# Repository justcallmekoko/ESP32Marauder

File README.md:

<!------>
<!------>
<!------>
<!---Shields/Badges https://shields.io/--->

# ESP32 Marauder

<p align="center">
  <b>A suite of WiFi/Bluetooth offensive and defensive tools for the ESP32</b>
  <br><br>

  <br>

  <br><br>
</p>

## Getting Started
Download the [latest release](https://github.com/justcallmekoko/ESP32Marauder/releases/latest) of the firmware.  

Check out the project [wiki](https://github.com/justcallmekoko/ESP32Marauder/wiki) for a full overview of the ESP32 Marauder

## FCC module identifiers

The Device Info screen reports the FCC ID of the radio module fitted to supported JustCallMeKoko hardware. This is the module identifier, not a claim that every carrier-board or enclosure configuration has a separate end-product grant.

| Hardware | Radio module | FCC ID |
| --- | --- | --- |
| Marauder v8, Marauder Mini v3, C5 Wardriver, C5 LowKey, BFFB v2 | ESP32-C5-WROOM-U | `2AC7Z-ESPC5WROOMU` |
| Marauder v4, v6, v6.1, v7, original Mini, Marauder Kit | ESP32-WROOM-32U | `2AC7Z-ESP32WROOM32U` |
| BFFB / Marauder Dev Board Pro | ESP32-WROOM-32E | `2AC7Z-ESP32WROOM32E` |

The legacy mappings are the closest modular approvals for the modules specified by the repository hardware designs. Confirm the module marking on a physical unit before using an FCC ID for labeling or compliance documentation. Third-party targets display `See hardware label` because their module or complete-device certification can vary by production revision.

# For Sale Now
You can buy the ESP32 Marauder using [this link](https://www.justcallmekokollc.com)

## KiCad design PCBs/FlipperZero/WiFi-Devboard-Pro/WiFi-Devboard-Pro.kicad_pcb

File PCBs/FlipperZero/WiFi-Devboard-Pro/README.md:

# Parts

- Header Pin x8: [C2883805](https://www.lcsc.com/product-detail/Pin-Headers_XKB-Connectivity-X6511WVS-08H-C60D48R1_C2883805.html)
- Header Pin x10: [C2883807](https://www.lcsc.com/product-detail/Pin-Headers_XKB-Connectivity-X6511WVS-10H-C60D48R1_C2883807.html)
- Alternative Header: [M20-8771246](https://www.mouser.com/ProductDetail/Harwin/M20-8771246?qs=WS5Jv%252B%252Bx1qWzrNY%252Bb2U9JQ%3D%3D&countryCode=US&currencyCode=USD)
  - or [M20-8771042](https://www.mouser.com/ProductDetail/Harwin/M20-8771042?qs=%252Bk6%2F5FB6qrlBSpg9%252Bi11Bg%3D%3D)
- Light Pipe: [PLP2-188](https://www.digikey.com/en/products/detail/bivar-inc/PLP2-188/5721973?utm_medium=email&utm_source=oce&utm_campaign=4251_OCE23RT&utm_content=productdetail_US&utm_cid=2955578&so=79456987&mkt_tok=MDI4LVNYSy01MDcAAAGJOBaFWa7m6RHsJZT6mWcYRd9LRyXmqis92EV7j5ftyM5NuNOSOPqUp292m0P5E3FKrEWCFuvb9fObSzuSvVMsopuOMPjO46ylCAR1IzCL)
- M2x6mm Round Top Screw: [97763A407](https://www.mcmaster.com/97763A407/)
- M2x8mm Countersunk Screw: [91294A005](https://www.mcmaster.com/91294A005/)
- M2 Threaded Insert: [94180A307](https://www.mcmaster.com/94180A307/)

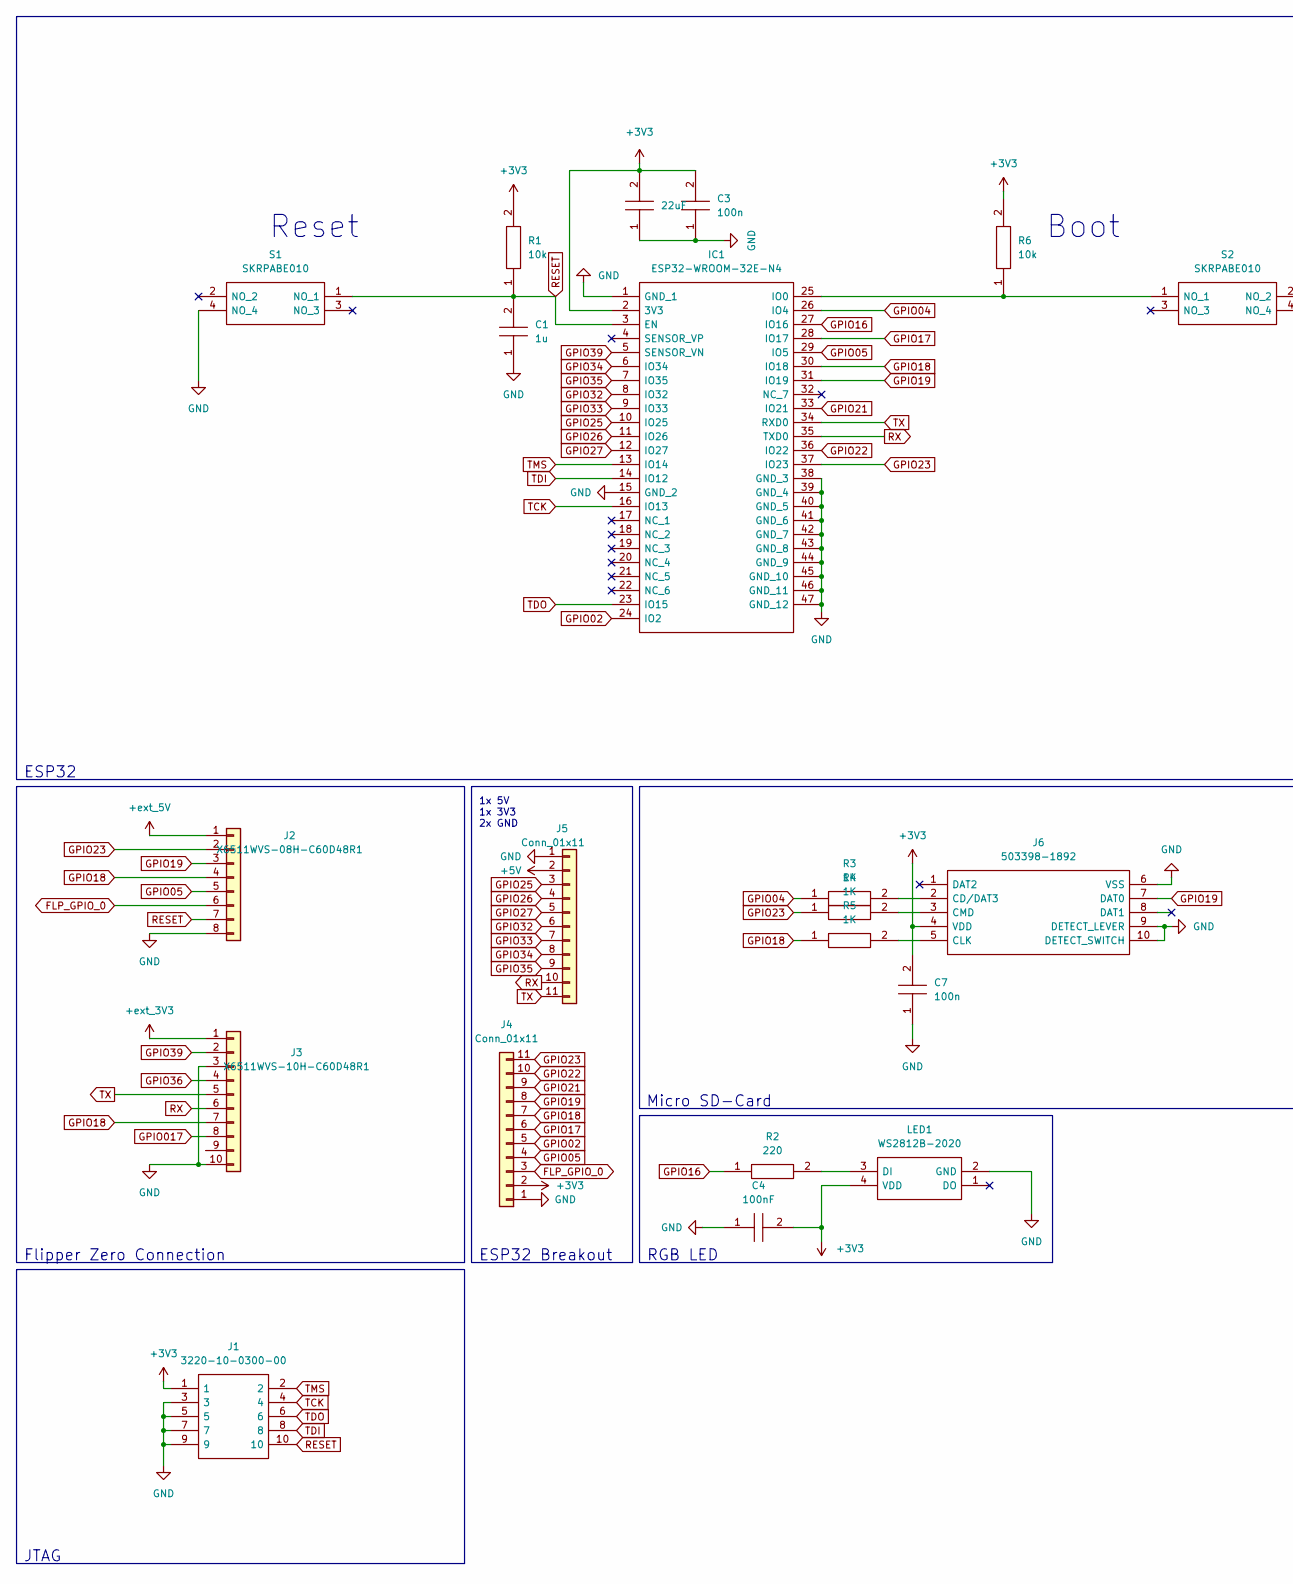
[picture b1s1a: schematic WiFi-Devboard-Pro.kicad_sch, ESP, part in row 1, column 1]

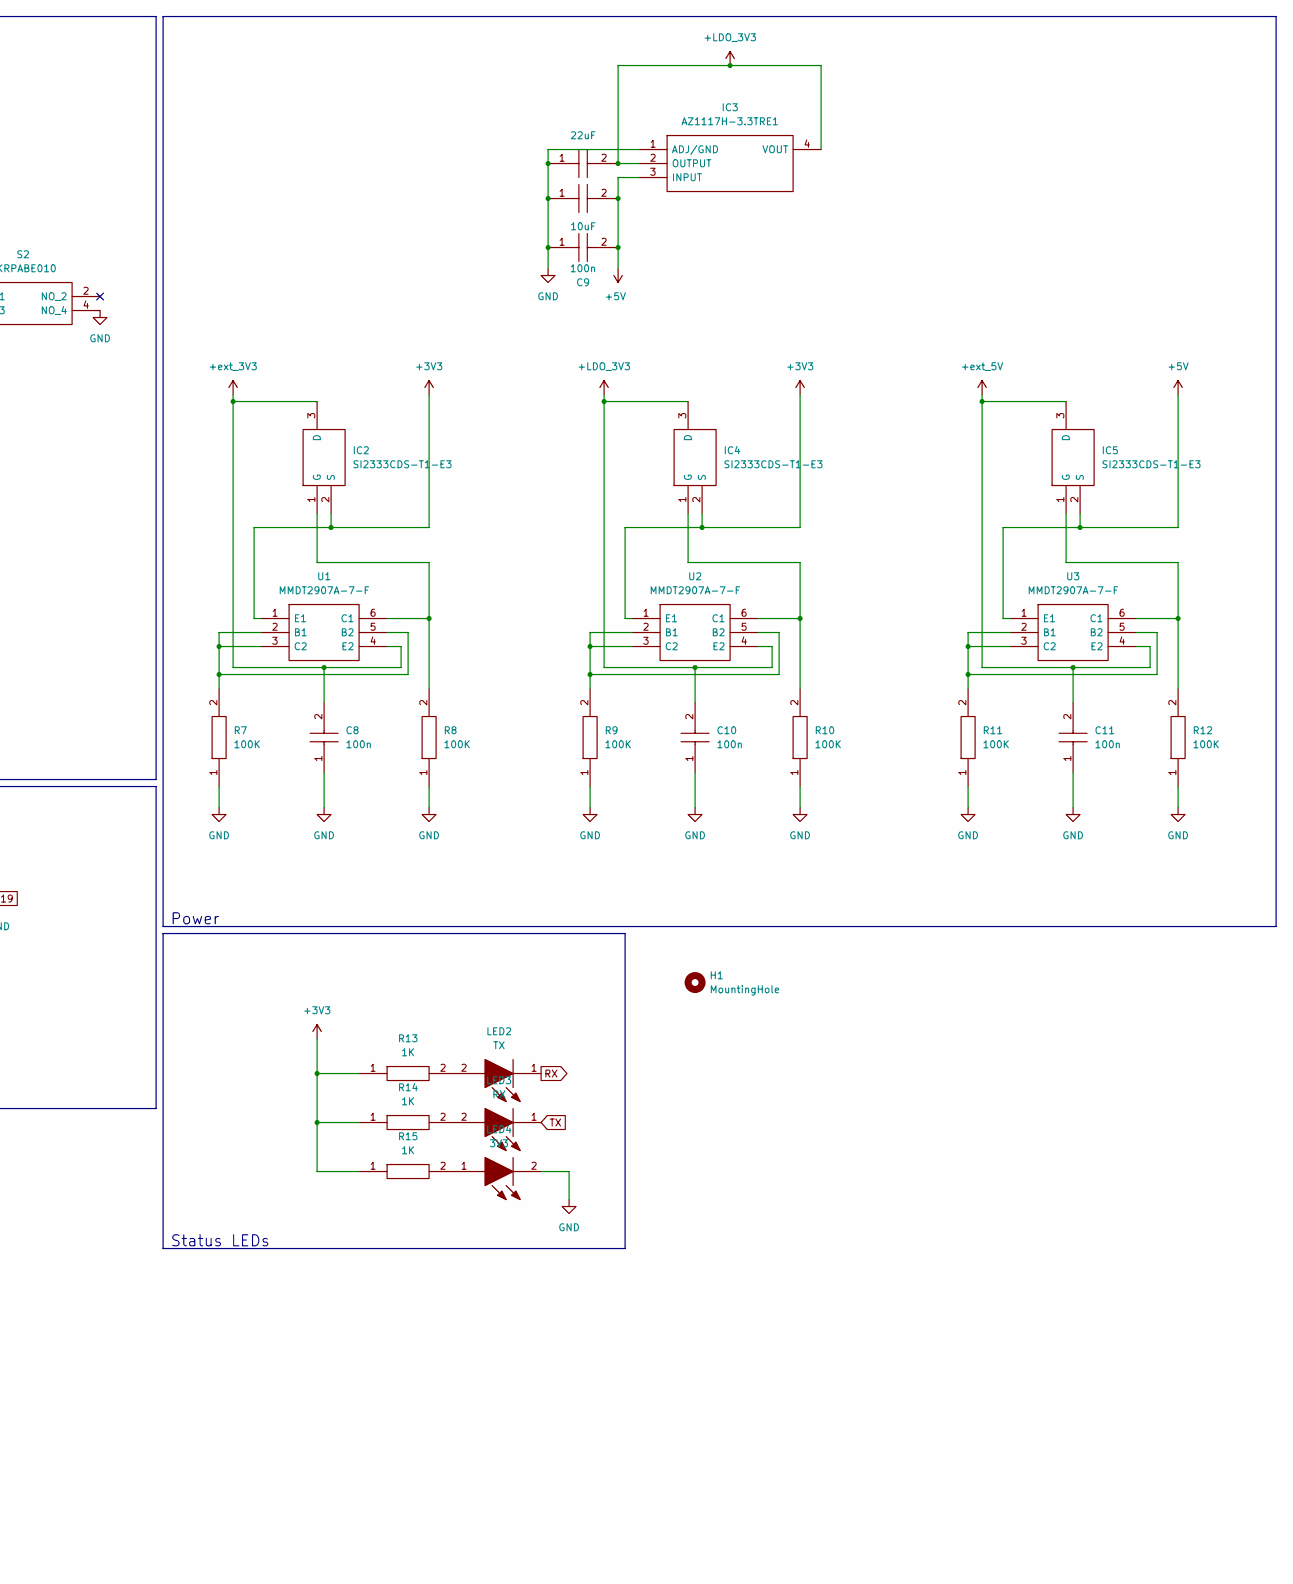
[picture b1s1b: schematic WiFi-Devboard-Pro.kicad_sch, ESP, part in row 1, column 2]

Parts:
C1: 1u; 0402; Manufacturer_Part_Number CL05A105KA5NQNC; Mouser Part Number 187-CL05A105KA5NQNC
C2, C5: 22uF; 0402; Manufacturer_Part_Number CM05X5R226M06AH080; Mouser Part Number 346-CM05X5R226M6AH80
C3, C7, C8, C9, C10, C11: 100n; 0402; Manufacturer_Part_Number CL05B104KO5NNNC; Mouser Part Number 187-CL05B104KO5NNNC
C4: 100nF; 0402; Manufacturer_Part_Number CC0402KRX7R7BB104; Mouser Part Number 603-CC402KRX7R7BB104
C6: 10uF; 0402; Manufacturer_Part_Number CL05A106MQ5NUNC; Mouser Part Number 187-CL05A106MQ5NUNC
H1: MountingHole
IC1: ESP32-WROOM-32E-N4; SMD-38P,18x25.5x3.1mm; Manufacturer_Part_Number ESP32-WROOM-32E-N4; Mouser Part Number 356-ESP32WRM32E132PH
IC2, IC4, IC5: SI2333CDS-T1-E3; SOT-23; Manufacturer_Part_Number DMP1045U-7; Mouser Part Number 621-DMP1045U-7
IC3: AZ1117H-3.3TRE1; SOT-223-3; Manufacturer_Part_Number AZ1117H-3.3TRE1; Mouser Part Number 621-AZ1117H-3.3TRE1
J1: 3220-10-0300-00; 322010030000; Manufacturer_Part_Number 3220-10-0300-00
J2: X6511WVS-08H-C60D48R1; SMD,P=2.54mm(交错脚); Manufacturer_Part_Number X6511WVS-08H-C60D48R2; LCSC Part Number C2883805
J3: X6511WVS-10H-C60D48R1; HUSRSP10W66P254_2500X250X850P; Manufacturer_Part_Number DZ254S-11-10-48; LCSC Part Number C2883807
J4, J5: Conn_01x11; SMD,P=2.54mm(交错脚)
J6: 503398-1892; SMD; Manufacturer_Part_Number 503398-1892; Mouser Part Number 538-503398-1892
LED1: WS2812B-2020; WS2812B2020; Manufacturer_Part_Number WS2812B-2020; LCSC Part Number C965555
LED2: TX; 0603; Manufacturer_Part_Number 19-217/Y5C-AP1Q2/3T; Mouser Part Number 638-19217Y5CAP1Q23T
LED3: RX; 0603; Manufacturer_Part_Number 19-217/Y5C-AP1Q2/3T; Mouser Part Number 638-19217Y5CAP1Q23T
LED4: 3V3; 0603; Manufacturer_Part_Number 19-217/R6C-AL1M2VY/3T; LCSC Part Number C84263
R1, R6: 10k; 0402; Manufacturer_Part_Number RC0402FR-0710KL; Mouser Part Number 603-RC0402FR-0710KL
R2: 220; 0402; Manufacturer_Part_Number RC0402FR-07220RL; Mouser Part Number 603-RC0402FR-07220RL
R3, R4, R5, R13, R14, R15: 1K; 0402; Manufacturer_Part_Number RC0402FR-071KL; Mouser Part Number 603-RC0402FR-071KL
R7, R8, R9, R10, R11, R12: 100K; 0402; Manufacturer_Part_Number RC0402FR-07100KL; Mouser Part Number 603-RC0402FR-07100KL
S1, S2: SKRPABE010; SMD; Manufacturer_Part_Number SKRPABE010; Mouser Part Number 688-SKRPAB
U1, U2, U3: MMDT2907A-7-F; SOT65P210X110-6N; Manufacturer_Part_Number MMDT2907A-7-F; Mouser Part Number 621-MMDT2907A-F

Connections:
+3V3: C2.2, C3.2, C4.2, C7.2, IC1.2 (3V3), IC2.2 (S), IC4.2 (S), J1.1, J4.2, J6.4 (VDD), LED1.4 (VDD), R1.2, R6.2, R13.1, R14.1, R15.1, U1.1 (E1), U2.1 (E1)
+5V: C6.2, C9.2, IC3.3 (INPUT), IC5.2 (S), J5.2, U3.1 (E1)
+LDO_3V3: C5.2, C10.2, IC3.2 (OUTPUT), IC3.4 (VOUT), IC4.3 (D), U2.4 (E2)
+ext_3V3: C8.2, IC2.3 (D), J3.1, U1.4 (E2)
+ext_5V: C11.2, IC5.3 (D), J2.1, U3.4 (E2)
FLP_GPIO_0: J2.6, J4.3
GND: C1.1, C2.1, C3.1, C4.1, C5.1, C6.1, C7.1, C8.1, C9.1, C10.1, C11.1, IC1.1 (GND_1), IC1.15 (GND_2), IC1.38 (GND_3), IC1.39 (GND_4), IC1.40 (GND_5), IC1.41 (GND_6), IC1.42 (GND_7), IC1.43 (GND_8), IC1.44 (GND_9), IC1.45 (GND_10), IC1.46 (GND_11), IC1.47 (GND_12), IC3.1 (ADJ/GND), J1.3, J1.5, J1.7, J1.9, J2.8, J3.3, J3.10, J4.1, J5.1, J6.6 (VSS), J6.9 (DETECT_LEVER), J6.10 (DETECT_SWITCH), LED1.2 (GND), LED4.2, R7.1, R8.1, R9.1, R10.1, R11.1, R12.1, S1.4 (NO), S2.4 (NO)
GPIO02: IC1.24 (IO2), J4.5
GPIO04: IC1.26 (IO4), R3.1
GPIO05: IC1.29 (IO5), J2.5, J4.4
GPIO16: IC1.27 (IO16), R2.1
GPIO17: IC1.28 (IO17), J4.6
GPIO017: J3.8
GPIO18: IC1.30 (IO18), J2.4, J3.7, J4.7, R5.1
GPIO19: IC1.31 (IO19), J2.3, J4.8, J6.7 (DAT0)
GPIO21: IC1.33 (IO21), J4.9
GPIO22: IC1.36 (IO22), J4.10
GPIO23: IC1.37 (IO23), J2.2, J4.11, R4.1
GPIO25: IC1.10 (IO25), J5.3
GPIO26: IC1.11 (IO26), J5.4
GPIO27: IC1.12 (IO27), J5.5
GPIO32: IC1.8 (IO32), J5.6
GPIO33: IC1.9 (IO33), J5.7
GPIO34: IC1.6 (IO34), J5.8
GPIO35: IC1.7 (IO35), J5.9
GPIO36: J3.4
GPIO39: IC1.5 (SENSOR_VN), J3.2
unnamed: IC1.25 (IO0), R6.1, S2.1 (NO)
unnamed: IC2.1 (G), R8.2, U1.6 (C1)
unnamed: IC4.1 (G), R10.2, U2.6 (C1)
unnamed: IC5.1 (G), R12.2, U3.6 (C1)
unnamed: J6.2 (CD/DAT3), R3.2
unnamed: J6.3 (CMD), R4.2
unnamed: J6.5 (CLK), R5.2
unnamed: LED1.3 (DI), R2.2
unnamed: LED2.2, R13.2
unnamed: LED3.2, R14.2
unnamed: LED4.1, R15.2
unnamed: R7.2, U1.2 (B1), U1.3 (C2), U1.5 (B2)
unnamed: R9.2, U2.2 (B1), U2.3 (C2), U2.5 (B2)
unnamed: R11.2, U3.2 (B1), U3.3 (C2), U3.5 (B2)
RESET: C1.2, IC1.3 (EN), J1.10, J2.7, R1.1, S1.1 (NO)
RX: IC1.35 (TXD0), J3.6, J5.10, LED2.1
TCK: IC1.16 (IO13), J1.4
TDI: IC1.14 (IO12), J1.8
TDO: IC1.23 (IO15), J1.6
TMS: IC1.13 (IO14), J1.2
TX: IC1.34 (RXD0), J3.5, J5.11, LED3.1

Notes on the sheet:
ESP32 Breakout
Status LEDs
Boot
Micro SD-Card
1x 5V 1x 3V3 2x GND
Reset
Power
RGB LED
Flipper Zero Connection
ESP32
JTAG

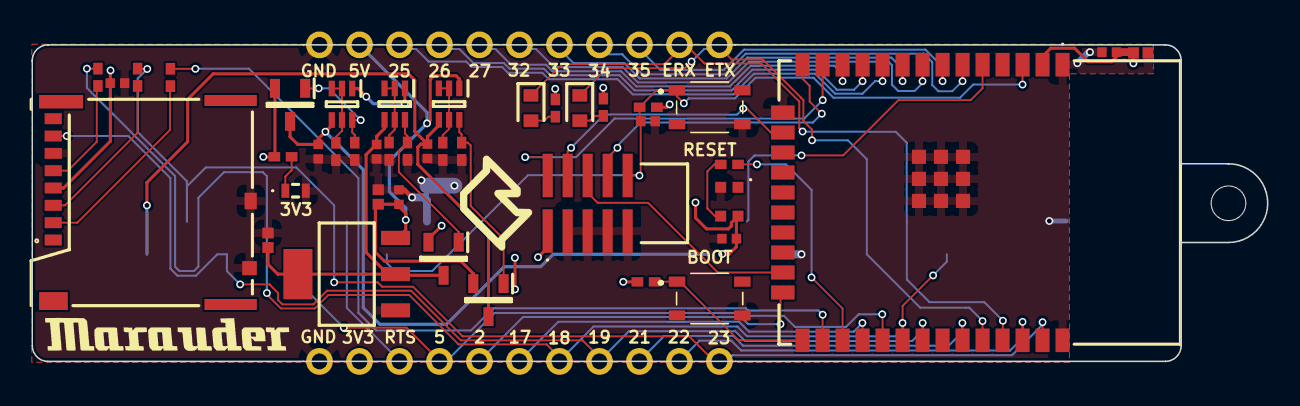
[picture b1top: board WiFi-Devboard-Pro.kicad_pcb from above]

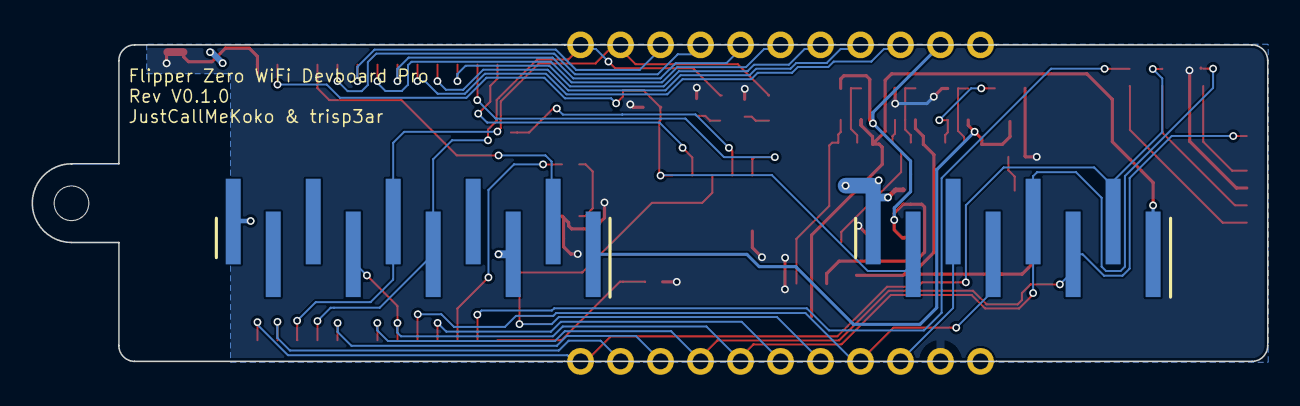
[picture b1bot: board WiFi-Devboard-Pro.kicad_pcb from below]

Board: 2 copper layers, 78.5 x 20.1 mm, 46 parts (2 on the bottom side), 46 nets.

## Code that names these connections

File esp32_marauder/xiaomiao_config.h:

#pragma once
//=================================================================
// 小喵掌机 (XiaoMiao) 板型配置 —— 单一真相源
// for ESP32 Marauder (继承官方 MARAUDER_MINI 分支)
//=================================================================
//
// 设计原理:
//   本文件在 configs.h 所有官方 #ifdef MARAUDER_MINI 块执行完毕之后
//   被 #include 进来 (见 configs.h 末尾), 通过 #undef + #define
//   覆盖引脚与屏幕布局, 使小喵硬件配置生效。
//   因此 configs.h 中任何官方 Mini 配置块都 *不需要* 修改 ——
//   上游 configs.h 更新后, 本地只需保留:
//     1) BOARD TARGETS 区的一行:  #define MARAUDER_XIAOMIAO
//     2) configs.h 末尾的一行:    #include "xiaomiao_config.h"
//     3) 本文件 xiaomiao_config.h
//   即可选择 "MARAUDER_XIAOMIAO" 板型直接编译适配。
//
// 使用方法 (任何 Marauder 版本):
//   1. 将本文件放到固件目录 (与 configs.h 同级)。
//   2. 打开 configs.h, 在 //// BOARD TARGETS 区注释掉其它板型,
//      并添加一行:   #define MARAUDER_XIAOMIAO
//   3. 在 configs.h 的 //// HARDWARE NAMES 块里加:
//        #elif defined(MARAUDER_XIAOMIAO)
//          #define HARDWARE_NAME "XiaoMiao Mini"
//   4. 在 configs.h 最末尾 (#endif 之前) 加:
//        #if defined(MARAUDER_XIAOMIAO)
//          #include "xiaomiao_config.h"
//        #endif
//   5. (可选) 在 //// MEMORY LOWER LIMIT STUFF 里加:
//        #elif defined(MARAUDER_XIAOMIAO)
//          #define MEM_LOWER_LIM 10000
//   6. 确认 TFT_eSPI 库 User_Setup_Select.h 选择了
//      User_Setup_marauder_mini.h (沿用官方 Mini 的 ST7735 配置)。
//
// 硬件信息:
//   MCU      : ESP32
//   屏幕      : 1.8" ST7735 160x128 横屏 (ST7735_GREENTAB3, BGR)
//   TF卡      : MicroSD, 与屏幕共享 VSPI 总线
//   按键      : 6键 (上/下/左/右/A确认/B返回)
//   LED      : NeoPixel (与官方 Mini 一致, GPIO25)
//   串口      : GPS 用 Serial2 (外部模块, 可选)
//
// 引脚定义:
//   屏幕: SCK=18 MOSI=23 CS=5 DC=4 RST=-1(不用) BL=直连电源(软件不控)
//   TF卡: SCK=18 MOSI=23 MISO=19 CS=22
//   按键: 上=IO2 下=IO13 左=IO27 右=IO35 A=IO34 B=IO12
//   注: GPIO34/35 为输入-only 引脚, 无内部上拉, 依赖 PCB 外部上拉电阻
//=================================================================

// ---- 0. 板型继承: 让所有 #ifdef MARAUDER_MINI 代码路径自动生效 ----
#ifndef MARAUDER_MINI
  #define MARAUDER_MINI
#endif

// ---- 0b. IDF 版本标记 ----
// ESP32 Arduino Core 3.x 使用 IDF 5.x, 必须走 HAS_IDF_3 兼容路径
// (WiFiScan/esp32_marauder.ino 等据此走 Core 3.x 分支)
#ifndef HAS_IDF_3
  #define HAS_IDF_3
#endif

// ---- 1. 硬件名称 ----
#ifdef HARDWARE_NAME
  #undef HARDWARE_NAME
#endif
#define HARDWARE_NAME "XiaoMiao Mini"

// ---- 2. 按键引脚覆盖 ----
// 官方 Mini 只有 5 键 (L/C/U/R/D); 小喵为 6 键, 增加 B(返回)。
// B_BTN 用 #if defined(B_BTN) 守卫, 避免官方 Mini (未定义 B_BTN) 误编译。
#ifdef L_BTN
  #undef L_BTN
#endif
#ifdef C_BTN
  #undef C_BTN
#endif
#ifdef U_BTN
  #undef U_BTN
#endif
#ifdef R_BTN
  #undef R_BTN
#endif
#ifdef D_BTN
  #undef D_BTN
#endif
#ifdef B_BTN
  #undef B_BTN
#endif

#define L_BTN 27
#define C_BTN 34   // A键 = 确认/选择
#define U_BTN 2
#define R_BTN 35
#define D_BTN 13
#define B_BTN 12   // B键 = 返回上级菜单

#ifdef HAS_L
  #undef HAS_L
#endif
#ifdef HAS_R
  #undef HAS_R
#endif
#ifdef HAS_U
  #undef HAS_U
#endif
#ifdef HAS_D
  #undef HAS_D
#endif
#ifdef HAS_C
  #undef HAS_C
#endif
#ifdef HAS_B
  #undef HAS_B
#endif
#define HAS_L
#define HAS_R
#define HAS_U
#define HAS_D
#define HAS_C
#define HAS_B   // 启用 B 键对象实例化与轮询

// ---- 3. 按键上拉配置 ----
// 所有按键: PCB 外部上拉, 按下时=LOW。
// Switches.cpp: pinMode(pin, INPUT_PULLUP/INPUT_PULLDOWN) 对 GPIO34/35
// (input-only) 的上下拉请求会被硬件忽略, 退化为纯 INPUT, 由外部上拉决定电平。
// getButtonState(): pullup=true 时 LOW=按下, 故全部用 true。
#ifdef L_PULL
  #undef L_PULL
#endif
#ifdef C_PULL
  #undef C_PULL
#endif
#ifdef U_PULL
  #undef U_PULL
#endif
#ifdef R_PULL
  #undef R_PULL
#endif
#ifdef D_PULL
  #undef D_PULL
#endif
#ifdef B_PULL
  #undef B_PULL
#endif

#define L_PULL true
#define C_PULL true   // GPIO34 input-only, 外部上拉, LOW=按下
#define U_PULL true
#define R_PULL true   // GPIO35 input-only, 外部上拉, LOW=按下
#define D_PULL true
#define B_PULL true

// ---- 4. 屏幕引脚覆盖 ----
#ifdef TFT_MISO
  #undef TFT_MISO
#endif
#ifdef TFT_MOSI
  #undef TFT_MOSI
#endif
#ifdef TFT_SCLK
  #undef TFT_SCLK
#endif
#ifdef TFT_CS
  #undef TFT_CS
#endif
#ifdef TFT_DC
  #undef TFT_DC
#endif
#ifdef TFT_RST
  #undef TFT_RST
#endif
#ifdef TOUCH_CS
  #undef TOUCH_CS
#endif

#define TFT_MISO -1   // ST7735 doesn't read back (SD 卡 MISO 用 GPIO19)
#define TFT_MOSI 23
#define TFT_SCLK 18
#define TFT_CS   5
#define TFT_DC   4
#define TFT_RST  -1   // 不使用 MCU 控制复位, ST7735 自带 POR 上电复位
                      // GPIO19 被 SD 卡 MISO 占用, 不能用作 TFT_RST
// TFT_BL: 背光直连电源, 无软件控制。不在此 #define, 让 TFT_eSPI 的
// User_Setup_marauder_mini.h 提供 TFT_BL=32 (官方 Mini 背光脚)。
// 对小喵 GPIO32 为空脚, digitalWrite(32, LOW) 无副作用, 编译正常。
#define TOUCH_CS -1

// ---- 5. 屏幕分辨率与方向覆盖 ----
// 1.8" ST7735 横屏有效分辨率: 160 wide x 128 tall
#ifdef DISP_W
  #undef DISP_W
#endif
#ifdef DISP_H
  #undef DISP_H
#endif
#ifdef SCREEN_ORIENTATION
  #undef SCREEN_ORIENTATION
#endif
#ifdef TFT_WIDTH
  #undef TFT_WIDTH
#endif
#ifdef TFT_HEIGHT
  #undef TFT_HEIGHT
#endif
#ifdef HEIGHT_1
  #undef HEIGHT_1
#endif
#ifdef WIDTH_1
  #undef WIDTH_1
#endif
#ifdef SCREEN_WIDTH
  #undef SCREEN_WIDTH
#endif
#ifdef SCREEN_HEIGHT
  #undef SCREEN_HEIGHT
#endif

#define DISP_W  160
#define DISP_H  128
#define SCREEN_ORIENTATION 3   // 3=landscape flipped (修复上下颠倒)
#define TFT_WIDTH   DISP_W     // 应用层横屏宽度
#define TFT_HEIGHT  DISP_H     // 应用层横屏高度
#define HEIGHT_1    DISP_H
#define WIDTH_1     DISP_W
#define SCREEN_WIDTH  DISP_W
#define SCREEN_HEIGHT DISP_H

// ---- 5b. 屏幕布局宏覆盖 (与 160x128 横屏匹配) ----
#ifdef GRAPH_VERT_LIM
  #undef GRAPH_VERT_LIM
#endif
#ifdef STANDARD_FONT_CHAR_LIMIT
  #undef STANDARD_FONT_CHAR_LIMIT
#endif
#ifdef TEXT_HEIGHT
  #undef TEXT_HEIGHT
#endif
#ifdef YMAX
  #undef YMAX
#endif
#ifdef FRAME_X
  #undef FRAME_X
#endif
#ifdef FRAME_Y
  #undef FRAME_Y
#endif
#ifdef FRAME_W
  #undef FRAME_W
#endif
#ifdef FRAME_H
  #undef FRAME_H
#endif
#ifdef REDBUTTON_X
  #undef REDBUTTON_X
#endif
#ifdef REDBUTTON_Y
  #undef REDBUTTON_Y
#endif
#ifdef REDBUTTON_W
  #undef REDBUTTON_W
#endif
#ifdef REDBUTTON_H
  #undef REDBUTTON_H
#endif
#ifdef GREENBUTTON_X
  #undef GREENBUTTON_X
#endif
#ifdef GREENBUTTON_Y
  #undef GREENBUTTON_Y
#endif
#ifdef GREENBUTTON_W
  #undef GREENBUTTON_W
#endif
#ifdef GREENBUTTON_H
  #undef GREENBUTTON_H
#endif
#ifdef STATUS_BAR_WIDTH
  #undef STATUS_BAR_WIDTH
#endif

#define GRAPH_VERT_LIM          (DISP_H / 2 - 1)
#define STANDARD_FONT_CHAR_LIMIT (DISP_W / 6)
#define TEXT_HEIGHT             (DISP_H / 10)
#define YMAX                    DISP_H
#define FRAME_X 80
#define FRAME_Y 48
#define FRAME_W 110
#define FRAME_H 44
#define REDBUTTON_X FRAME_X
#define REDBUTTON_Y FRAME_Y
#define REDBUTTON_W (FRAME_W / 2)
#define REDBUTTON_H FRAME_H
#define GREENBUTTON_X (REDBUTTON_X + REDBUTTON_W)
#define GREENBUTTON_Y FRAME_Y
#define GREENBUTTON_W (FRAME_W / 2)
#define GREENBUTTON_H FRAME_H
#define STATUS_BAR_WIDTH        (DISP_H / 16)

// ---- 6. SD 卡引脚覆盖 ----
// 与屏幕共享 VSPI 总线: SCK/MOSI 相同, MISO=19, CS=22
#ifdef SD_CS
  #undef SD_CS
#endif
#ifdef SD_SCK
  #undef SD_SCK
#endif
#ifdef SD_MISO
  #undef SD_MISO
#endif
#ifdef SD_MOSI
  #undef SD_MOSI
#endif

#define SD_CS   22
#define SD_SCK  18
#define SD_MISO 19
#define SD_MOSI 23

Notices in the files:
README.md:
License: MIT
